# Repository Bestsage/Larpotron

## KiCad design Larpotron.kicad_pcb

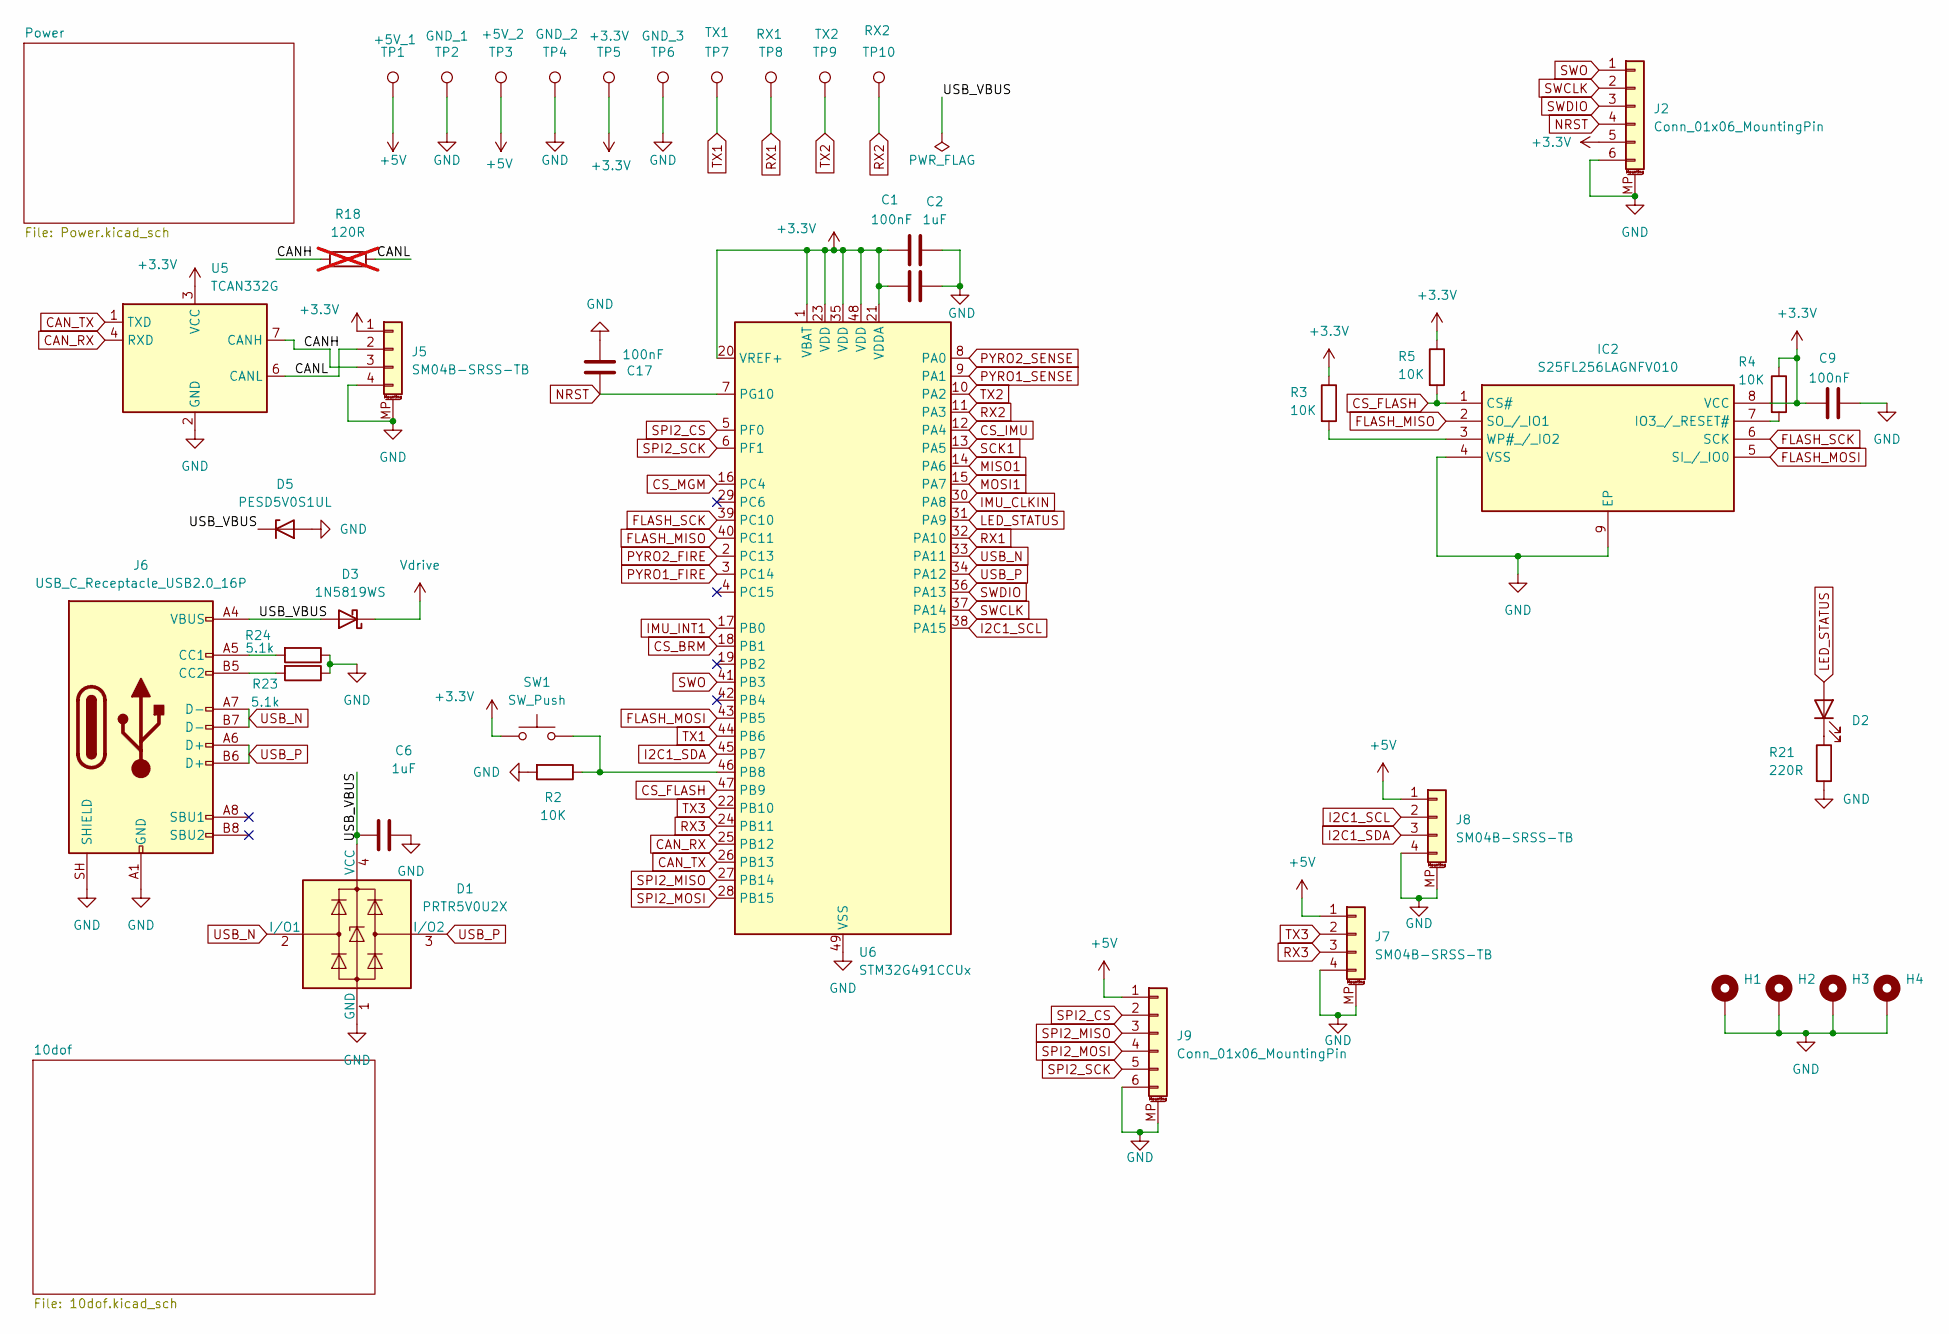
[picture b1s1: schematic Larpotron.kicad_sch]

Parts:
C1, C9, C17: 100nF; C_0402_1005Metric; Mouser Part Number 81-GRM155R71C104KA88; DigiKey 490-10698-1-ND
C2: 1uF; C_0402_1005Metric; Mouser Part Number 81-GRM155R61C105KA2D; DigiKey 490-GRM155R61C105KA12DCT-ND
C6: 1uF; C_0603_1608Metric; Mouser Part Number 187-CL10B105KA8NNNC; DigiKey 1276-1184-1-ND
D1: PRTR5V0U2X; SOT-143; Mouser Part Number 771-PRTR5V0U2X215; DigiKey 568-4140-1-ND
D2: Wurth Elektronik 150080YS75000; LED_0805_2012Metric; Mouser Part Number 710-150080YS75000; DigiKey 732-150080YS75000-ND
D3: 1N5819WS; D_SOD-323; Mouser Part Number 621-B5819WS-7-F; DigiKey B5819WS-7-DFICT-ND
D5: PESD5V0S1UL; D_SOD-882
H1, H2, H3, H4: MountingHole_Pad; MountingHole_2.7mm_M2.5_ISO14580_Pad
IC2: S25FL256LAGNFV010; SON127P800X600X80-9N-D; Mouser Part Number 727-S25FL256LAGNV010
J2: Conn_01x06_MountingPin; JST_SH_SM06B-SRSS-TB_1x06-1MP_P1.00mm_Horizontal
J5, J7, J8: SM04B-SRSS-TB; JST_SH_SM04B-SRSS-TB_1x04-1MP_P1.00mm_Horizontal; Mouser Part Number 306-SM04BSRSSTBLFSN; DigiKey 455-SM04B-SRSS-TBCT-ND
J6: USB_C_Receptacle_USB2.0_16P; USB_C_Receptacle_GCT_USB4105-xx-A_16P_TopMnt_Horizontal; Mouser Part Number 640-USB4105-GF-A; DigiKey 2073-USB4105-GF-ACT-ND
J9: Conn_01x06_MountingPin; JST_SH_SM06B-SRSS-TB_1x06-1MP_P1.00mm_Horizontal; Mouser Part Number 306-M06BSRSSTBLFSNPP; DigiKey 455-SM06B-SRSS-TBCT-ND
R2, R3, R4: 10K; R_0603_1608Metric; Mouser Part Number 603-RC0603FR-0710KL; DigiKey 311-10.0KHRCT-ND
R5: 10K; R_0402_1005Metric; Mouser Part Number 603-RC0402FR-0710KL; DigiKey 311-10.0KLRCT-ND
R18: 120R; R_0805_2012Metric_Pad1.20x1.40mm_HandSolder; Mouser Part Number 603-RC0805FR-07120RL; DigiKey 311-120CRCT-ND; not fitted
R21: 220R; R_0603_1608Metric; Mouser Part Number 603-RC0603FR-07220RL; DigiKey 311-220HRCT-ND
R23, R24: 5.1k; R_0603_1608Metric; Mouser Part Number 603-RC0603FR-075K1L; DigiKey 311-5.10KHRCT-ND
SW1: SW_Push; SW_SPST_PTS810
TP1: +5V_1; TestPoint_Pad_1.5x1.5mm
TP2: GND_1; TestPoint_Pad_1.5x1.5mm
TP3: +5V_2; TestPoint_Pad_1.5x1.5mm
TP4: GND_2; TestPoint_Pad_1.5x1.5mm
TP5: +3.3V; TestPoint_Pad_1.5x1.5mm
TP6: GND_3; TestPoint_Pad_1.5x1.5mm
TP7: TX1; TestPoint_Pad_1.5x1.5mm
TP8: RX1; TestPoint_Pad_1.5x1.5mm
TP9: TX2; TestPoint_Pad_1.5x1.5mm
TP10: RX2; TestPoint_Pad_1.5x1.5mm
U5: TCAN332G; TSOT-23-8; Mouser Part Number 595-TCAN332GDCNT; DigiKey 296-44390-1-ND
U6: STM32G491CCUx; QFN-48-1EP_7x7mm_P0.5mm_EP5.6x5.6mm; Mouser Part Number 511-STM32G491CCU6; DigiKey 497-STM32G491CCU6-ND

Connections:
+3.3V: C1.2, C2.2, C9.2, IC2.8 (VCC), J2.5, J5.1, R3.1, R4.1, R5.1, SW1.1, TP5.1 (1_1), U5.3 (VCC), U6.1 (VBAT), U6.20 (VREF+), U6.21 (VDDA), U6.23 (VDD), U6.35 (VDD), U6.48 (VDD); also elsewhere on the board
+5V: J7.1, J8.1, J9.1, TP1.1 (1_1), TP3.1 (1_1); also elsewhere on the board
/CANH: J5.3, R18.1, U5.7 (CANH)
/CANL: J5.2, R18.2, U5.6 (CANL)
/USB_VBUS: C6.2, D1.4 (VCC), D3.2 (A), D5.1 (K), J6.A4 (VBUS), J6.A9 (VBUS), J6.B4 (VBUS), J6.B9 (VBUS)
CAN_RX: U5.4 (RXD), U6.25 (PB12)
CAN_TX: U5.1 (TXD), U6.26 (PB13)
CS_BRM: U6.18 (PB1); also elsewhere on the board
CS_FLASH: IC2.1 (CS#), R5.2, U6.47 (PB9)
CS_IMU: U6.12 (PA4); also elsewhere on the board
CS_MGM: U6.16 (PC4); also elsewhere on the board
FLASH_MISO: IC2.2 (SO_/_IO1), U6.40 (PC11)
FLASH_MOSI: IC2.5 (SI_/_IO0), U6.43 (PB5)
FLASH_SCK: IC2.6 (SCK), U6.39 (PC10)
GND: C1.1, C2.1, C6.1, C9.1, C17.2, D1.1 (GND), D5.2 (A), H1.1 (1_1), H2.1 (1_1), H3.1 (1_1), H4.1 (1_1), IC2.4 (VSS), IC2.9 (EP), J2.6, J2.MP (MountPin), J5.4, J5.MP (MountPin), J6.A1 (GND), J6.A12 (GND), J6.B1 (GND), J6.B12 (GND), J6.SH (SHIELD), J7.4, J7.MP (MountPin), J8.4, J8.MP (MountPin), J9.6, J9.MP (MountPin), R2.2, R21.2, R23.1, R24.1, TP2.1 (1_1), TP4.1 (1_1), TP6.1 (1_1), U5.2 (GND), U6.49 (VSS); also elsewhere on the board
I2C1_SCL: J8.2, U6.38 (PA15); also elsewhere on the board
I2C1_SDA: J8.3, U6.45 (PB7); also elsewhere on the board
IMU_CLKIN: U6.30 (PA8); also elsewhere on the board
IMU_INT1: U6.17 (PB0); also elsewhere on the board
LED_STATUS: D2.2 (A), U6.31 (PA9)
MISO1: U6.14 (PA6); also elsewhere on the board
MOSI1: U6.15 (PA7); also elsewhere on the board
NRST: C17.1, J2.4, U6.7 (PG10)
unnamed: D2.1 (K), R21.1
unnamed: IC2.7 (IO3_/_RESET#), R4.2
unnamed: IC2.3 (WP#_/_IO2), R3.2
unnamed: J6.A5 (CC1), R24.2
unnamed: J6.B5 (CC2), R23.2
unnamed: R2.1, SW1.2, U6.46 (PB8)
PYRO1_FIRE: U6.3 (PC14); also elsewhere on the board
PYRO1_SENSE: U6.9 (PA1); also elsewhere on the board
PYRO2_FIRE: U6.2 (PC13); also elsewhere on the board
PYRO2_SENSE: U6.8 (PA0); also elsewhere on the board
RX1: TP8.1 (1_1), U6.32 (PA10)
RX2: TP10.1 (1_1), U6.11 (PA3)
RX3: J7.3, U6.24 (PB11)
SCK1: U6.13 (PA5); also elsewhere on the board
SPI2_CS: J9.2, U6.5 (PF0)
SPI2_MISO: J9.3, U6.27 (PB14)
SPI2_MOSI: J9.4, U6.28 (PB15)
SPI2_SCK: J9.5, U6.6 (PF1)
SWCLK: J2.2, U6.37 (PA14)
SWDIO: J2.3, U6.36 (PA13)
SWO: J2.1, U6.41 (PB3)
TX1: TP7.1 (1_1), U6.44 (PB6)
TX2: TP9.1 (1_1), U6.10 (PA2)
TX3: J7.2, U6.22 (PB10)
USB_N: D1.2 (I/O1), J6.A7 (D-), J6.B7 (D-), U6.33 (PA11)
USB_P: D1.3 (I/O2), J6.A6 (D+), J6.B6 (D+), U6.34 (PA12)
Vdrive: D3.1 (K); also elsewhere on the board

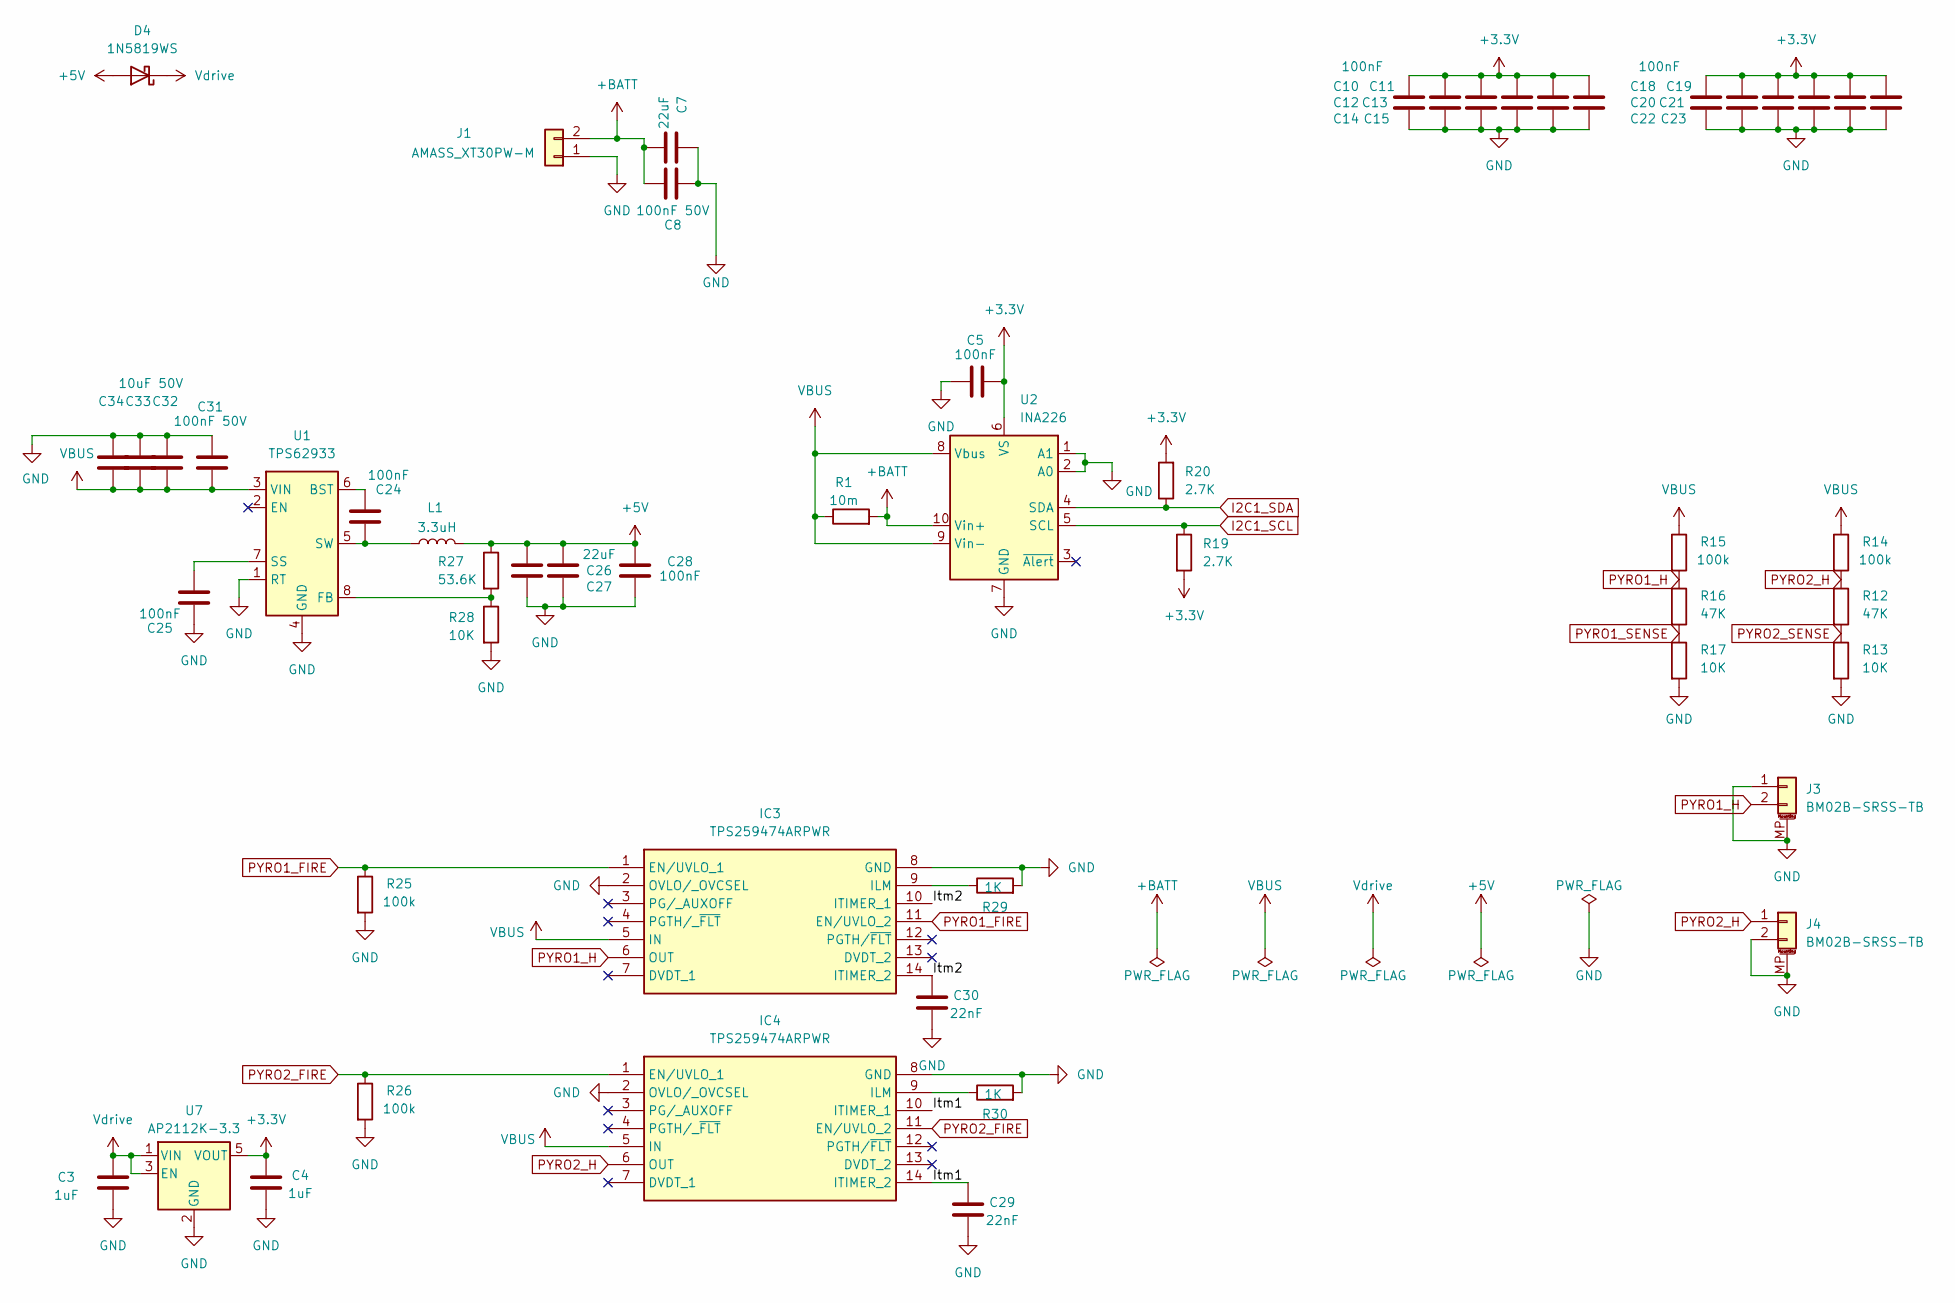
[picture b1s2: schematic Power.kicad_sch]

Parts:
C3, C4: 1uF; C_0402_1005Metric; Mouser Part Number 81-GRM155R61C105KA2D; DigiKey 490-GRM155R61C105KA12DCT-ND
C5, C10, C11, C12, C13, C14, C15, C18, C19, C20, C21, C22, C23, C24, C25, C28: 100nF; C_0402_1005Metric; Mouser Part Number 81-GRM155R71C104KA88; DigiKey 490-10698-1-ND
C7: 22uF; C_1206_3216Metric; Mouser Part Number 187-CL31A226KAHNNNE; DigiKey 1276-3047-1-ND
C8, C31: 100nF 50V; C_0402_1005Metric; Manufacturer_Part_Number GRM155R71H104KE14D
C26, C27: 22uF; C_0805_2012Metric; Mouser Part Number 187-CL10A106KP8NNNC; DigiKey 1276-CL10A106KP8NNNC-ND
C29, C30: 22nF; C_0402_1005Metric; Mouser Part Number 81-GRM155R61C105KA2D; DigiKey 490-GRM155R61C105KA12DCT-ND
C32, C33, C34: 10uF 50V; C_1206_3216Metric; Manufacturer_Part_Number GRM155R71H104KE14D
D4: 1N5819WS; D_SOD-323; Mouser Part Number 621-B5819WS-7-F; DigiKey B5819WS-7-DFICT-ND
IC3, IC4: TPS259474ARPWR; Mouser Part Number 595-TPS259474ARPWR
J1: AMASS_XT30PW-M; AMASS_XT30PW-M_1x02_P2.50mm_Horizontal; Manufacturer_Part_Number XT30PW-M; LCSC C431092
J3, J4: BM02B-SRSS-TB; JST_SH_BM02B-SRSS-TB_1x02-1MP_P1.00mm_Vertical; Mouser Part Number 306-BM02BSRSSTBLFSNP; DigiKey 455-BM02B-SRSS-TBCT-ND
L1: 3.3uH; L_Bourns-SRN4018
R1: 10m; R_1206_3216Metric; Mouser Part Number 71-WSL1206R0100FEA; DigiKey WSLC-.01CT-ND
R12, R16: 47K; R_0402_1005Metric; Mouser Part Number 603-RC0603FR-0747KL; DigiKey 311-47.0KHRCT-ND
R13, R17: 10K; R_0402_1005Metric; Mouser Part Number 603-RC0603FR-0710KL; DigiKey 311-10.0KHRCT-ND
R14, R15, R25, R26: 100k; R_0402_1005Metric; Mouser Part Number 603-RC0603FR-07100KL; DigiKey 311-100KHRCT-ND
R19, R20: 2.7K; R_0402_1005Metric; Mouser Part Number 603-RC0603FR-072K7L; DigiKey 311-2.70KHRCT-ND
R27: 53.6K; R_0603_1608Metric; Mouser Part Number 603-RC0603FR-072K7L; DigiKey 311-2.70KHRCT-ND
R28: 10K; R_0603_1608Metric; Mouser Part Number 603-RC0603FR-072K7L; DigiKey 311-2.70KHRCT-ND
R29, R30: 1K; R_0402_1005Metric; Mouser Part Number 603-RC0603FR-072K7L; DigiKey 311-2.70KHRCT-ND
U1: TPS62933; SOT-583-8
U2: INA226; TSSOP-10_3x3mm_P0.5mm; Mouser Part Number 595-INA226AIDGSR; DigiKey 296-29034-1-ND
U7: AP2112K-3.3; SOT-23-5

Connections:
+3.3V: C4.1, C5.1, C10.1, C11.1, C12.1, C13.1, C14.1, C15.1, C18.1, C19.1, C20.1, C21.1, C22.1, C23.1, R19.2, R20.2, U2.6 (VS), U7.5 (VOUT); also elsewhere on the board
+5V: C26.1, C27.1, C28.2, D4.2 (A), L1.2, R27.1; also elsewhere on the board
+BATT: C7.2, C8.1, J1.2, R1.2, U2.10 (Vin+)
/Power/Itm1: C29.1, IC4.10 (ITIMER_1), IC4.14 (ITIMER_2)
/Power/Itm2: C30.1, IC3.10 (ITIMER_1), IC3.14 (ITIMER_2)
GND: C3.2, C4.2, C5.2, C7.1, C8.2, C10.2, C11.2, C12.2, C13.2, C14.2, C15.2, C18.2, C19.2, C20.2, C21.2, C22.2, C23.2, C25.2, C26.2, C27.2, C28.1, C29.2, C30.2, C31.2, C32.2, C33.2, C34.2, IC3.2 (OVLO/_OVCSEL), IC3.8 (GND), IC4.2 (OVLO/_OVCSEL), IC4.8 (GND), J1.1, J3.1, J3.MP (MountPin), J4.2, J4.MP (MountPin), R13.2, R17.2, R25.2, R26.2, R28.2, R29.2, R30.2, U1.1 (RT), U1.4 (GND), U2.1 (A1), U2.2 (A0), U2.7 (GND), U7.2 (GND); also elsewhere on the board
I2C1_SCL: R19.1, U2.5 (SCL); also elsewhere on the board
I2C1_SDA: R20.1, U2.4 (SDA); also elsewhere on the board
unnamed: IC3.9 (ILM), R29.1
unnamed: IC4.9 (ILM), R30.1
unnamed: C24.1, U1.6 (BST)
unnamed: R27.2, R28.1, U1.8 (FB)
unnamed: C25.1, U1.7 (SS)
unnamed: C24.2, L1.1, U1.5 (SW)
PYRO1_FIRE: IC3.1 (EN/UVLO_1), IC3.11 (EN/UVLO_2), R25.1; also elsewhere on the board
PYRO1_H: IC3.6 (OUT), J3.2, R15.2, R16.1
PYRO1_SENSE: R16.2, R17.1; also elsewhere on the board
PYRO2_FIRE: IC4.1 (EN/UVLO_1), IC4.11 (EN/UVLO_2), R26.1; also elsewhere on the board
PYRO2_H: IC4.6 (OUT), J4.1, R12.1, R14.2
PYRO2_SENSE: R12.2, R13.1; also elsewhere on the board
VBUS: C31.1, C32.1, C33.1, C34.1, IC3.5 (IN), IC4.5 (IN), R1.1, R14.1, R15.1, U1.3 (VIN), U2.8 (Vbus), U2.9 (Vin-)
Vdrive: C3.1, D4.1 (K), U7.1 (VIN), U7.3 (EN); also elsewhere on the board

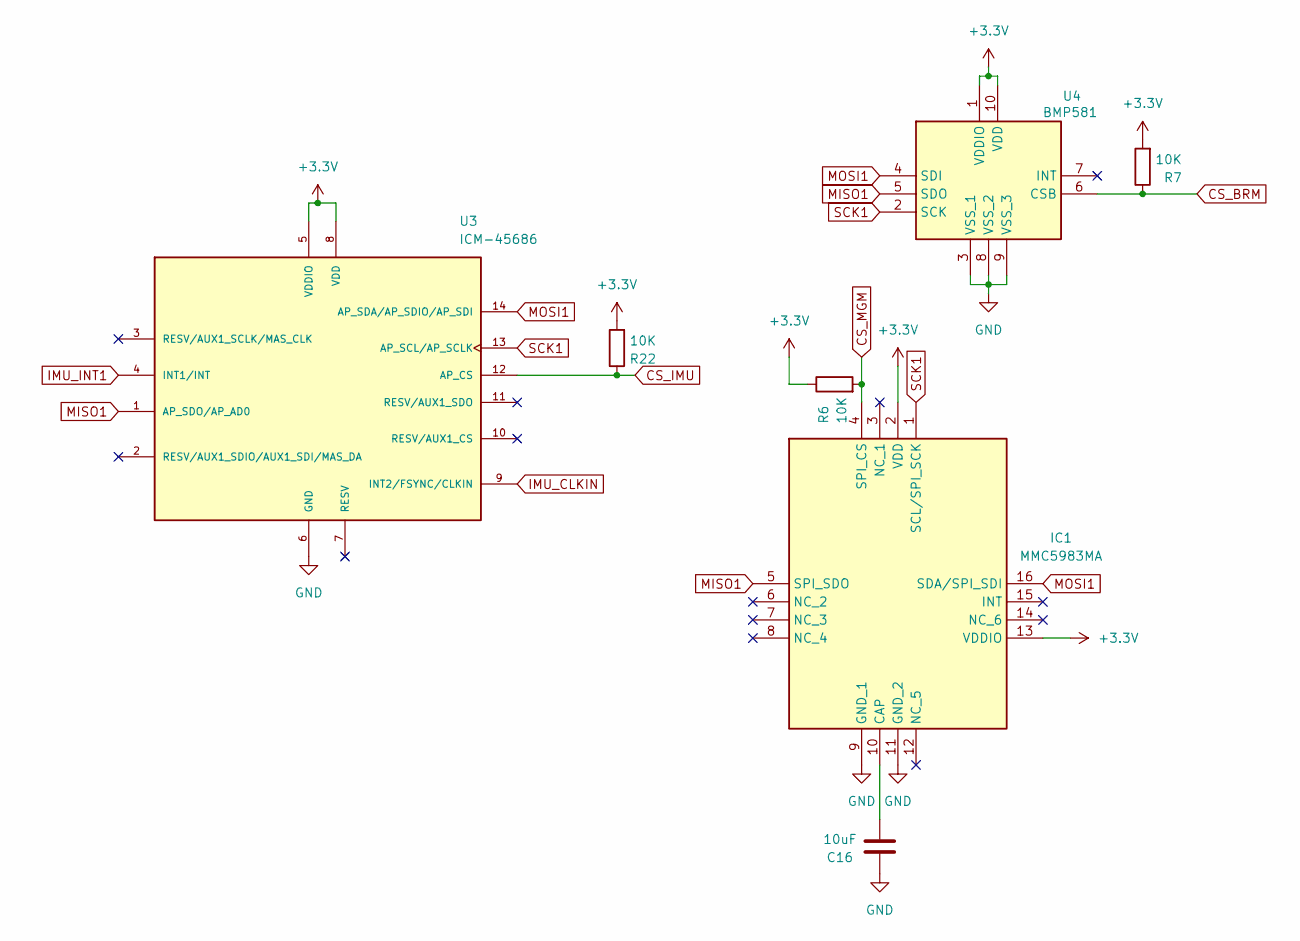
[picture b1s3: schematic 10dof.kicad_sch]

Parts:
C16: 10uF; C_0402_1005Metric; Mouser Part Number 187-CL10A106KP8NNNC; DigiKey 1276-CL10A106KP8NNNC-ND
IC1: MMC5983MA; Mouser Part Number 438-MMC5983MA
R6, R7, R22: 10K; R_0402_1005Metric; Mouser Part Number 603-RC0402FR-0710KL; DigiKey 311-10.0KLRCT-ND
U3: ICM-45686; IC_ICM-45686; MPN ICM-45686; DigiKey 1428-ICM-45686CT-ND
U4: BMP581; Mouser Part Number 262-BMP581

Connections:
+3.3V: IC1.2 (VDD), IC1.13 (VDDIO), R6.1, R7.2, R22.2, U3.5 (VDDIO), U3.8 (VDD), U4.1 (VDDIO), U4.10 (VDD); also elsewhere on the board
CS_BRM: R7.1, U4.6 (CSB); also elsewhere on the board
CS_IMU: R22.1, U3.12 (AP_CS); also elsewhere on the board
CS_MGM: IC1.4 (SPI_CS), R6.2; also elsewhere on the board
GND: C16.2, IC1.9 (GND_1), IC1.11 (GND_2), U3.6 (GND), U4.3 (VSS_1), U4.8 (VSS_2), U4.9 (VSS_3); also elsewhere on the board
IMU_CLKIN: U3.9 (INT2/FSYNC/CLKIN); also elsewhere on the board
IMU_INT1: U3.4 (INT1/INT); also elsewhere on the board
MISO1: IC1.5 (SPI_SDO), U3.1 (AP_SDO/AP_AD0), U4.5 (SDO); also elsewhere on the board
MOSI1: IC1.16 (SDA/SPI_SDI), U3.14 (AP_SDA/AP_SDIO/AP_SDI), U4.4 (SDI); also elsewhere on the board
unnamed: C16.1, IC1.10 (CAP)
SCK1: IC1.1 (SCL/SPI_SCK), U3.13 (AP_SCL/AP_SCLK), U4.2 (SCK); also elsewhere on the board

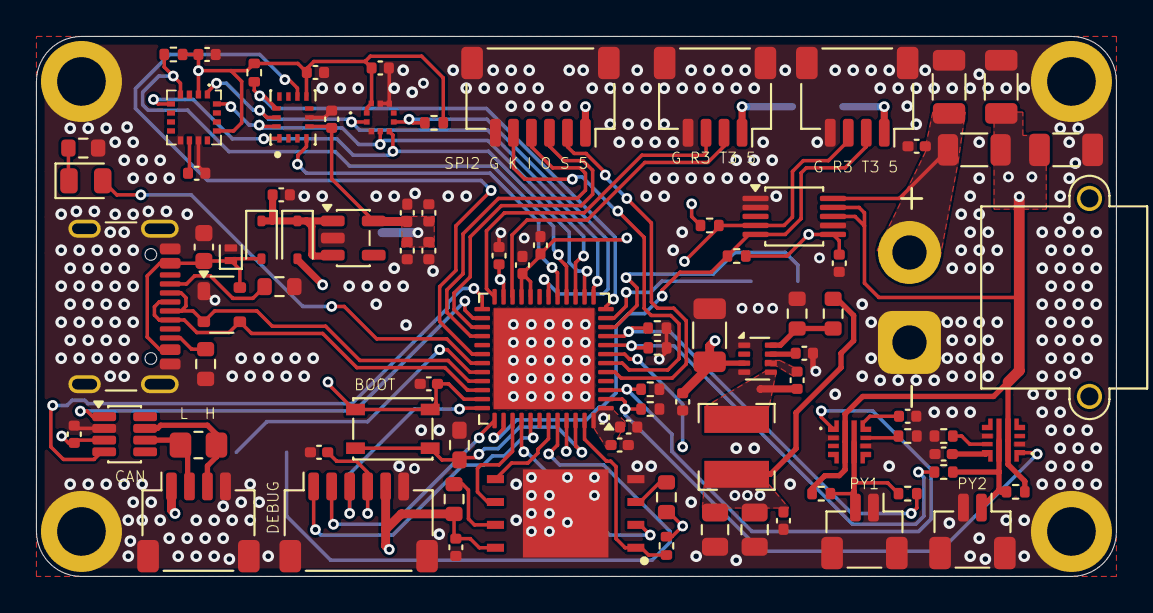
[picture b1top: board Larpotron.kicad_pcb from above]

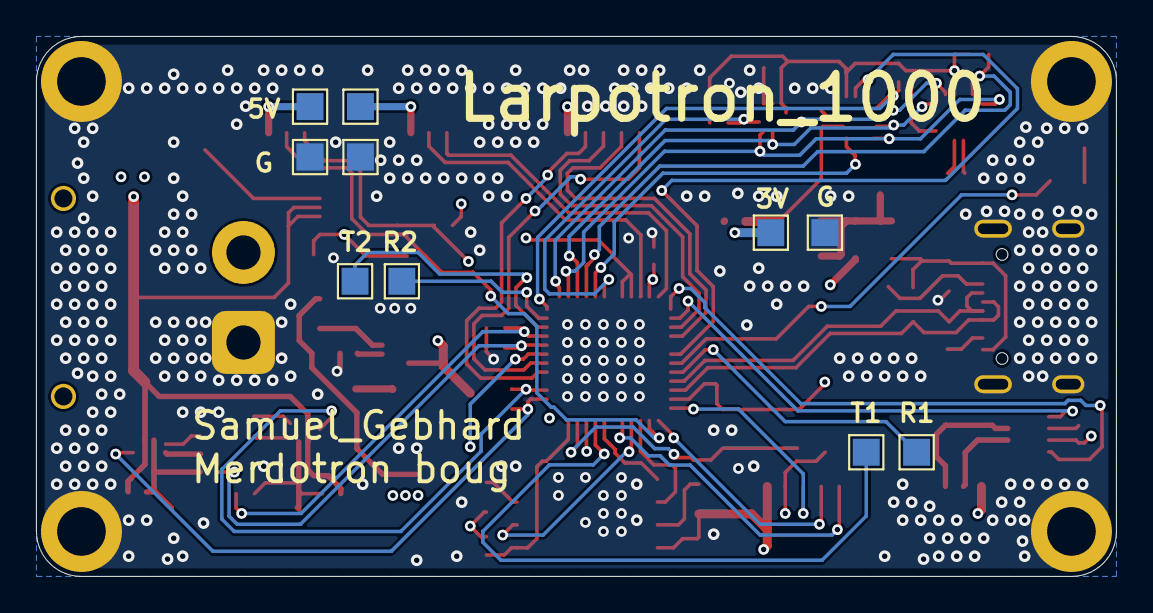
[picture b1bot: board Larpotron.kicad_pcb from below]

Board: 4 copper layers, 60.0 x 30.0 mm, 101 parts (10 on the bottom side), 63 nets.

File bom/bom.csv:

Reference,Qty,Value,Footprint,MPN,Manufacturer,DigiKey,DK_Stock,Mouser,MO_Stock,LCSC,LC_Stock,Chosen_Distributor,Datasheet,Validated,DNP,Notes
C2,1,1uF,0402,GRM155R61C105KA12D,Murata Electronics,490-GRM155R61C105KA12DCT-ND,,81-GRM155R61C105KA2D,,C52923,,,,,,
"C4,C3",2,22uF,1206,CL31A226KAHNNNE,Samsung Electro-Mechanics,1276-3047-1-ND,,187-CL31A226KAHNNNE,,C6119968,,,,,,
C6,1,1uF,0603,CL10B105KA8NNNC,Samsung Electro-Mechanics,1276-1184-1-ND,,187-CL10B105KA8NNNC,,C29936,,,,,,
"C9,C17,C1,C5,C15,C21,C12,C10,C20,C19,C14,C23,C13,C22,C18,C11",16,100nF,0402,GRM155R71C104KA88D,Murata Electronics,490-10698-1-ND,,81-GRM155R71C104KA88,,C1525,,,,,,
C16,1,10uF,0603,CL10A106KP8NNNC,Samsung Electro-Mechanics,1276-CL10A106KP8NNNC-ND,,187-CL10A106KP8NNNC,,C19702,,,,,,
D1,1,PRTR5V0U2X,SOT-143,"PRTR5V0U2X,215",Nexperia,568-4140-1-ND,,771-PRTR5V0U2X215,,C2827688,,,https://assets.nexperia.com/documents/data-sheet/PRTR5V0U2X.pdf,,,
D2,1,Wurth Elektronik 150080YS75000,0805,150080YS75000,Wurth Elektronik,732-150080YS75000-ND,,710-150080YS75000,,C2296,,,https://www.we-online.com/components/products/datasheet/1500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,,,"LCSC/JLCPCB Basic alt: KT-0805Y (C2296, jaune 590nm 0805)"
"D3,D4",2,1N5819WS,SOD-323,B5819WS-7-F,Diodes Incorporated,B5819WS-7-DFICT-ND,,621-B5819WS-7-F,,C2927280,,,https://datasheet.lcsc.com/lcsc/2204281430_Guangdong-Hottech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,,,
IC1,1,MMC5983MA,MMC5983MA,MMC5983MA,MEMSIC,1267-MMC5983MACT-ND,,438-MMC5983MA,,C404329,,,,,,
IC2,1,S25FL256LAGNFV010,SON127P800X600X80-9N-D,S25FL256LAGNFV010,Infineon,448-S25FL256LAGNFV010-ND,,727-S25FL256LAGNV010,,C1350629,,,https://componentsearchengine.com/Datasheets/2/S25FL256LAGNF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,,,
"IC3,IC4",2,FDC6326L,SOT95P280X110-6N,FDC6326L,onsemi,FDC6326LCT-ND,,512-FDC6326L,,C5310929,,,https://www.onsemi.com/pdf/datasheet/fdc6326l-d.pdf,,,
J1,1,AMASS_XT30PW-M,AMASS_XT30PW-M_1x02_P2.50mm_Horizontal,XT30PW-M,AMASS,,,,,C431092,,,,,,Non vendu chez Mouser/DigiKey — sourcer chez TME / LCSC / boutique RC
J2,1,BM05B-SRSS-TB,JST_SH_BM05B-SRSS-TB_1x05-1MP_P1.00mm_Vertical,BM05B-SRSS-TB(LF)(SN),JST,455-BM05B-SRSS-TBCT-ND,,306-BM05BSRSSTBLFSN,,C160391,,,,,,
"J4,J3",2,BM02B-SRSS-TB,JST_SH_BM02B-SRSS-TB_1x02-1MP_P1.00mm_Vertical,BM02B-SRSS-TB(LF)(SN),JST,455-BM02B-SRSS-TBCT-ND,,306-BM02BSRSSTBLFSNP,,C160388,,,,,,
J6,1,USB_C_Receptacle_USB2.0_16P,USB_C_Receptacle_GCT_USB4105-xx-A_16P_TopMnt_Horizontal,USB4105-GF-A,GCT,2073-USB4105-GF-ACT-ND,,640-USB4105-GF-A,,C3020560,,,https://www.usb.org/sites/default/files/documents/usb_type-c.zip,,,
"J8,J5,J7",3,SM04B-SRSS-TB,JST_SH_SM04B-SRSS-TB_1x04-1MP_P1.00mm_Horizontal,SM04B-SRSS-TB(LF)(SN),JST,455-SM04B-SRSS-TBCT-ND,,306-SM04BSRSSTBLFSN,,C160404,,,,,,
J9,1,Conn_01x06_MountingPin,JST_SH_SM06B-SRSS-TB_1x06-1MP_P1.00mm_Horizontal,SM06B-SRSS-TB(LF)(SN),JST,455-SM06B-SRSS-TBCT-ND,,306-M06BSRSSTBLFSNPP,,C160405,,,,,,
R1,1,10m,1206,WSL1206R0100FEA,Vishay Dale,WSLC-.01CT-ND,,71-WSL1206R0100FEA,,C601097,,,,,,
"R2,R4,R3,R11,R17,R10,R13,R8,R9",9,10K,0603,RC0603FR-0710KL,Yageo,311-10.0KHRCT-ND,,603-RC0603FR-0710KL,,C384294,,,,,,
"R5,R22,R7,R6",4,10K,0402,RC0402FR-0710KL,Yageo,311-10.0KLRCT-ND,,603-RC0402FR-0710KL,,C2902636,,,,,,
"R12,R16",2,47K,0603,RC0603FR-0747KL,Yageo,311-47.0KHRCT-ND,,603-RC0603FR-0747KL,,C844929,,,,,,
"R14,R15",2,100k,0603,RC0603FR-07100KL,Yageo,311-100KHRCT-ND,,603-RC0603FR-07100KL,,C25803,,,,,,
R18,1,120R,0805,RC0805FR-07120RL,Yageo,311-120CRCT-ND,,603-RC0805FR-07120RL,,C17437,,,,,,
"R20,R19",2,2.7K,0603,RC0603FR-072K7L,Yageo,311-2.70KHRCT-ND,,603-RC0603FR-072K7L,,C13167,,,,,,
R21,1,220R,0603,RC0603FR-07220RL,Yageo,311-220HRCT-ND,,603-RC0603FR-07220RL,,C22962,,,,,,
"R23,R24",2,5.1k,0603,RC0603FR-075K1L,Yageo,311-5.10KHRCT-ND,,603-RC0603FR-075K1L,,C23186,,,,,,
U1,1,AZ1117CH-3.3TRG1,SOT-223-3_TabPin2,AZ1117CH-3.3TRG1,Diodes Incorporated,AZ1117CH-3.3TRG1DICT-ND,,621-AZ1117CH-3.3TRG1,,C92102,,,https://4donline.ihs.com/images/VipMasterIC/IC/DIOD/DIOD-S-A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,,,
U2,1,INA226,TSSOP-10_3x3mm_P0.5mm,INA226AIDGSR,Texas Instruments,296-29034-1-ND,,595-INA226AIDGSR,,C49851,,,http://www.ti.com/lit/ds/symlink/ina226.pdf,,,
U3,1,ICM-45686,IC_ICM-45686,ICM-45686,TDK InvenSense,1428-ICM-45686CT-ND,,410-ICM-45686,,C22459454,,,https://snapeda.s3.amazonaws.com/datasheet/DS-000489+ICM-456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,,,
U4,1,BMP581,BMP581,BMP581,BOSCH,828-BMP581CT-ND,,262-BMP581,,C5362283,,,https://www.bosch-sensortec.com/media/boschsensortec/downloa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,,,
U5,1,TCAN332G,TSOT-23-8,TCAN332GDCNT,Texas Instruments,296-44390-1-ND,,595-TCAN332GDCNT,,C191007,,,http://www.ti.com/lit/ds/symlink/tcan337.pdf,,,
U6,1,STM32G491CCUx,QFN-48-1EP_7x7mm_P0.5mm_EP5.6x5.6mm,STM32G491CCU6,STMicroelectronics,497-STM32G491CCU6-ND,,511-STM32G491CCU6,,C2970035,,,https://www.st.com/resource/en/datasheet/stm32g491cc.pdf,,,
